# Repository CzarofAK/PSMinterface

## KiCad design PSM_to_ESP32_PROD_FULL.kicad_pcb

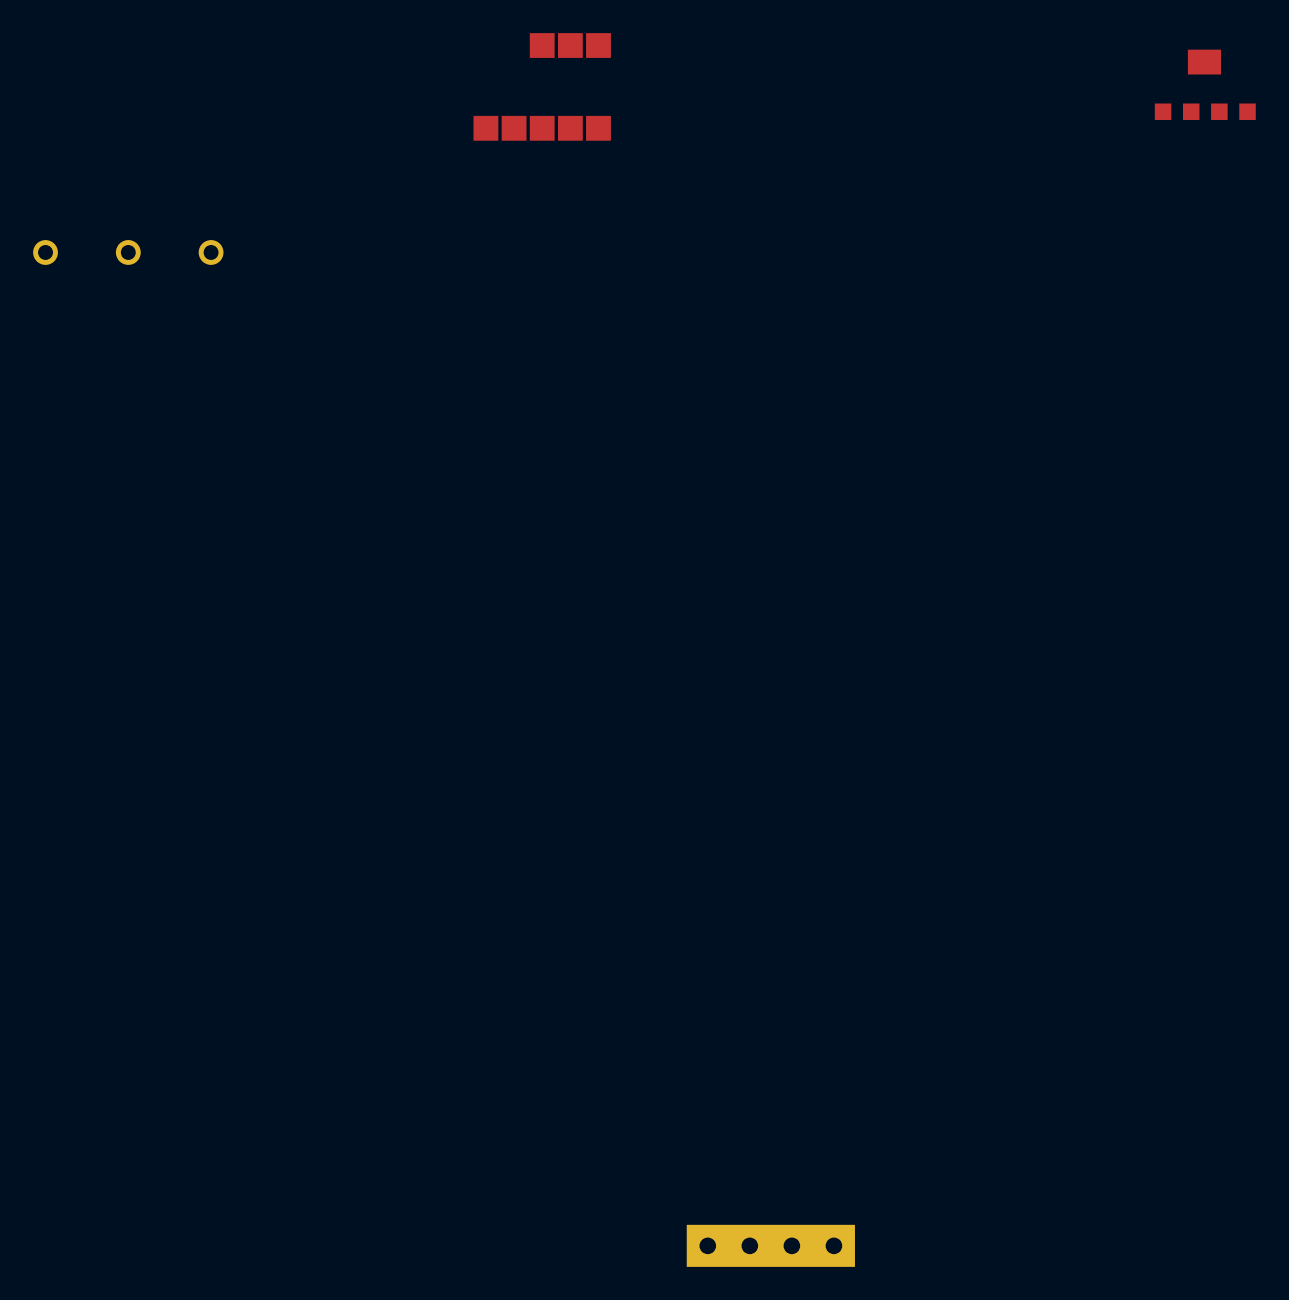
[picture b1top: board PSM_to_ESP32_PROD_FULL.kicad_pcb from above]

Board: 0 copper layers, 4 parts (0 on the bottom side), 3 nets, no tracks yet.

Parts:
J1: PSM_CONN; Connector_PSM
J2: ESP32_HDR; ESP32_DEVKIT
U_CAN: TJA1043
U_LDO: TLV70033; LD1117

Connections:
3V3: J2.1, U_CAN.6, U_LDO.2
5V: U_CAN.5, U_LDO.1
GND: J1.2, J2.2, U_CAN.4, U_LDO.5

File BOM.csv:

Ref,Qty,Description,Footprint
F1,1,Automotive fuse 1A, 5x20mm, slow-blow,FUSE_5X20
TVS_INPUT,1,Automotive TVS, unidirectional SMBJ58CA or equivalent,SMBJ
D1,1,Schottky diode, 60V, 3A, SMC package (reverse polarity),SMC
U_PWR,1,Automotive DC-DC converter (9-36V -> 5V isolated or non-isolated), e.g. Murata NMA0505SC,MODULE_CUSTOM
U_LDO,1,Automotive-grade 3.3V LDO (e.g. TI TLV70033 or MCP1700A), SOT-23-5,SOT-23-5
U_CAN,1,Automotive CAN transceiver TJA1043 or NXP TJA1051/ISOTP capable, SOIC-8,SOIC-8
CMC,1,Common mode choke for CAN (automotive rated),CMC_SMD
TVS_CAN,1,CAN pair TVS (two-line transorb array, SOT23-6),SOT-23-6
OPTOS,10,Optocoupler (logic-speed, Avago/ADI ACPL-063L or similar automotive grade),SOIC-8_OR_SMD
Q1,10,MOSFET 2N7002 alternative automotive-level, SOT-23,SOT-23
R_values,50,Resistors assorted (10k,22k,33k,5.6k,47k) 1206/0603,0603
C_values,20,Capacitors assorted (100nF,1uF,10uF,47uF) MLCC automotive grade,0603/1206
CONN_PSM,1,Mating automotive connector / pigtail (to match PSM harness),CONN_PSM_CUSTOM
HDR,1,2.54mm header for ESP32 DevKitC mounting or optional female header,HDR_2.54_ESP32
SHIELD_CLAMP,1,Shield grounding resistor 10R for CAN shield to chassis,R_0603
